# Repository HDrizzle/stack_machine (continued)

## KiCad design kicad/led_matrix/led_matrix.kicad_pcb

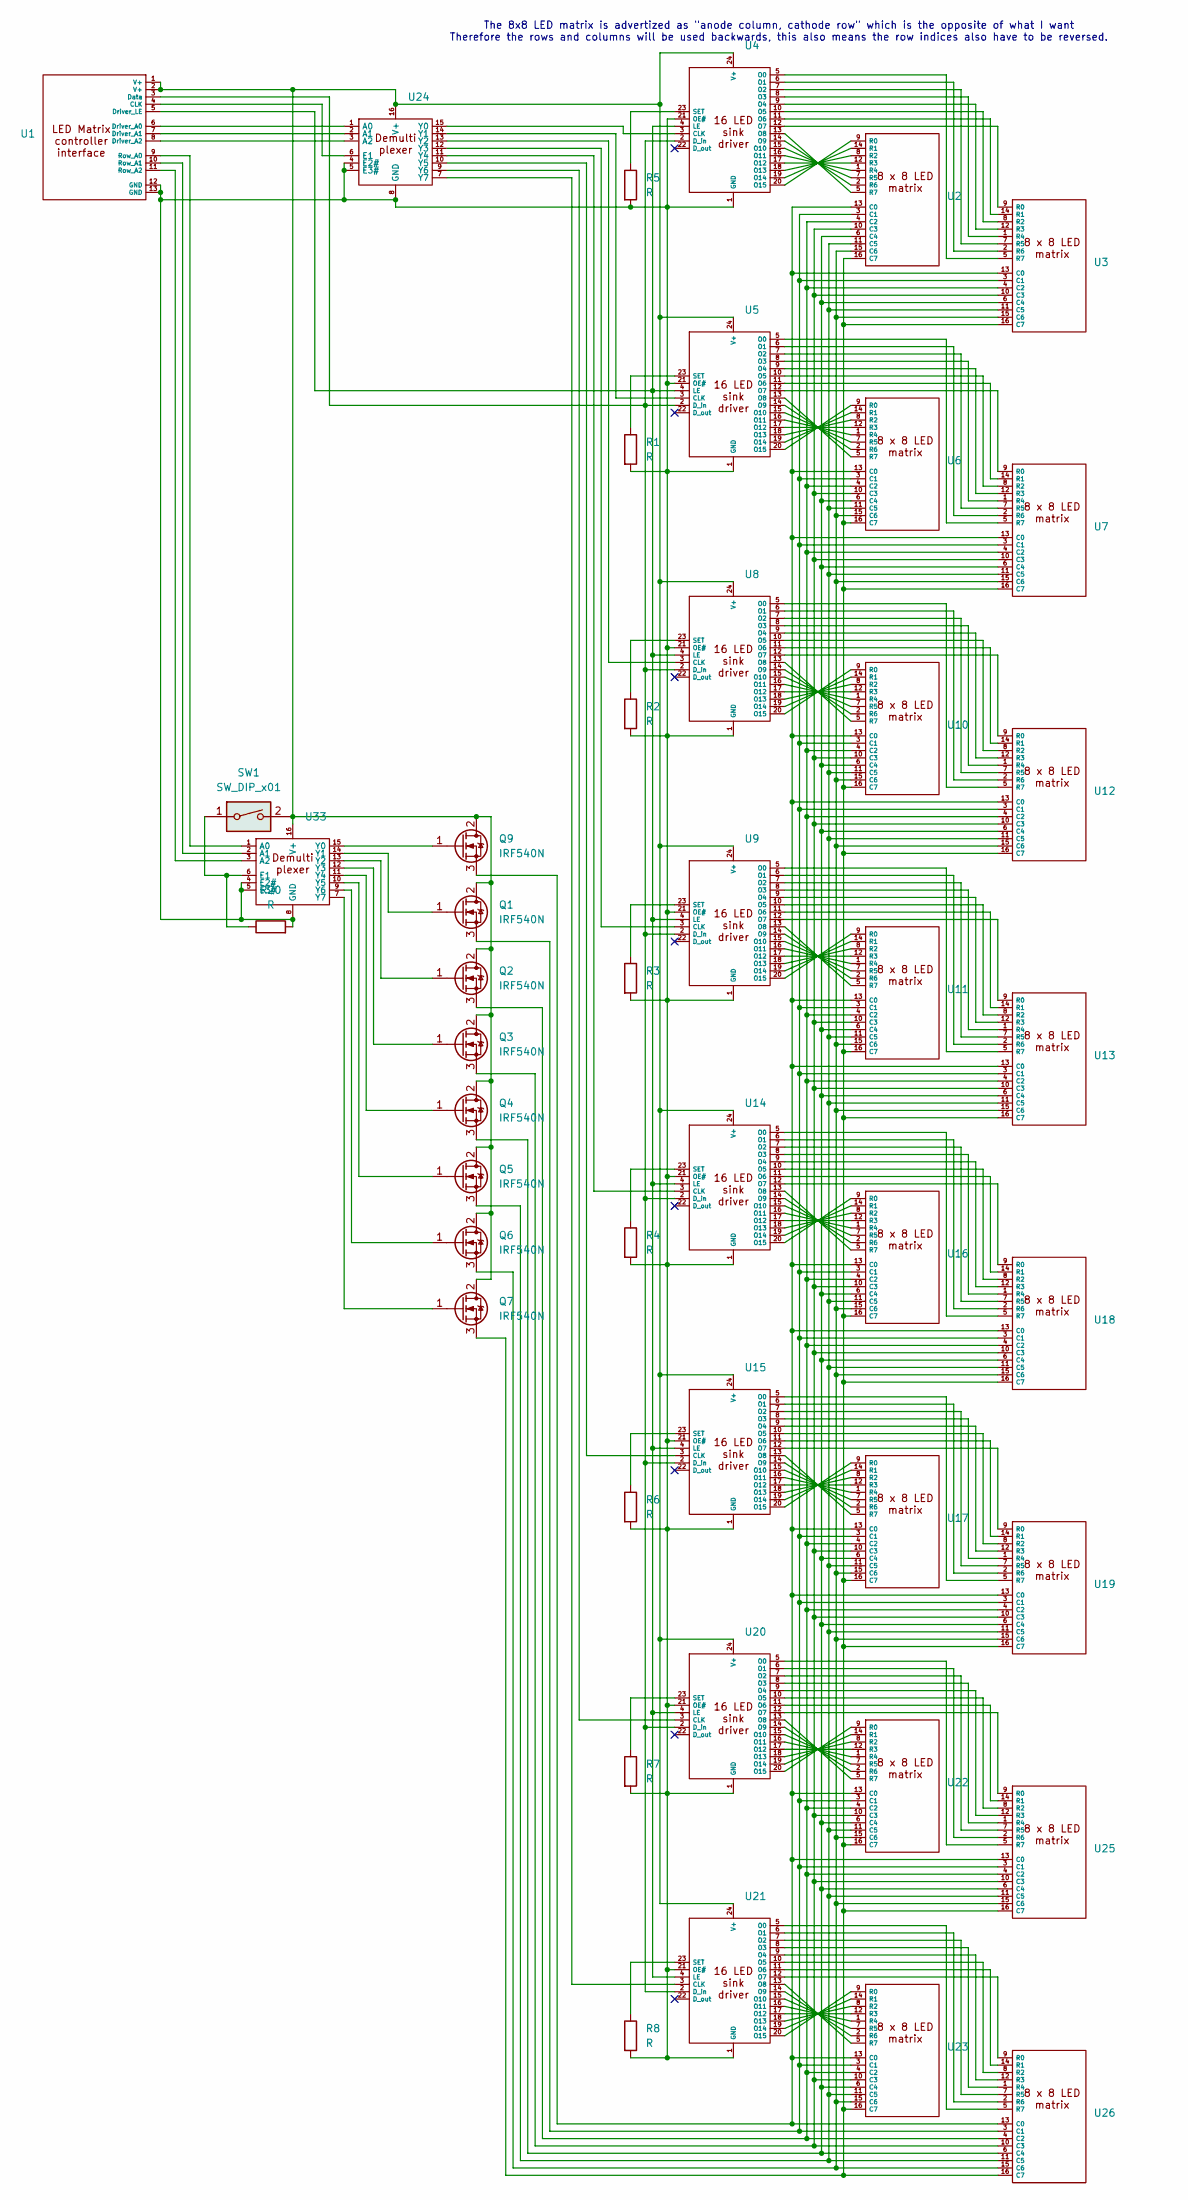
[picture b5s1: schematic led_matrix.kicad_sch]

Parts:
Q1, Q2, Q3, Q4, Q5, Q6, Q7, Q9: IRF540N; TO-220-3_Vertical
R1, R2, R3, R4, R5, R6, R7, R8, R20: R; 0.4_pitch_resistor
SW1: SW_DIP_x01; SW_DIP_SPSTx01_Slide_6.7x4.1mm_W7.62mm_P2.54mm_LowProfile
U1: PinHeader_1x13_P2.54mm_Vertical
U2, U3, U6, U7, U10, U11, U12, U13, U16, U17, U18, U19, U22, U23, U25, U26: 8_x_8_led_matrix_KWM-30881CVB
U4, U5, U8, U9, U14, U15, U20, U21: DIP-24_W7.62mm
U24, U33: DIP-16_W7.62mm

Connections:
unnamed: Q1.2 (D), Q2.2 (D), Q3.2 (D), Q4.2 (D), Q5.2 (D), Q6.2 (D), Q7.2 (D), Q9.2 (D), SW1.2, U1.1 (V+), U1.2 (V+), U4.24 (V+), U5.24 (V+), U8.24 (V+), U9.24 (V+), U14.24 (V+), U15.24 (V+), U20.24 (V+), U21.24 (V+), U24.16 (V+), U33.16 (V+)
unnamed: Q1.1 (G), U33.14 (Y1)
unnamed: Q1.3 (S), U2.3 (C1), U3.3 (C1), U6.3 (C1), U7.3 (C1), U10.3 (C1), U11.3 (C1), U12.3 (C1), U13.3 (C1), U16.3 (C1), U17.3 (C1), U18.3 (C1), U19.3 (C1), U22.3 (C1), U23.3 (C1), U25.3 (C1), U26.3 (C1)
unnamed: Q2.1 (G), U33.13 (Y2)
unnamed: Q2.3 (S), U2.4 (C2), U3.4 (C2), U6.4 (C2), U7.4 (C2), U10.4 (C2), U11.4 (C2), U12.4 (C2), U13.4 (C2), U16.4 (C2), U17.4 (C2), U18.4 (C2), U19.4 (C2), U22.4 (C2), U23.4 (C2), U25.4 (C2), U26.4 (C2)
unnamed: Q3.1 (G), U33.12 (Y3)
unnamed: Q3.3 (S), U2.10 (C3), U3.10 (C3), U6.10 (C3), U7.10 (C3), U10.10 (C3), U11.10 (C3), U12.10 (C3), U13.10 (C3), U16.10 (C3), U17.10 (C3), U18.10 (C3), U19.10 (C3), U22.10 (C3), U23.10 (C3), U25.10 (C3), U26.10 (C3)
unnamed: Q4.1 (G), U33.11 (Y4)
unnamed: Q4.3 (S), U2.6 (C4), U3.6 (C4), U6.6 (C4), U7.6 (C4), U10.6 (C4), U11.6 (C4), U12.6 (C4), U13.6 (C4), U16.6 (C4), U17.6 (C4), U18.6 (C4), U19.6 (C4), U22.6 (C4), U23.6 (C4), U25.6 (C4), U26.6 (C4)
unnamed: Q5.1 (G), U33.10 (Y5)
unnamed: Q5.3 (S), U2.11 (C5), U3.11 (C5), U6.11 (C5), U7.11 (C5), U10.11 (C5), U11.11 (C5), U12.11 (C5), U13.11 (C5), U16.11 (C5), U17.11 (C5), U18.11 (C5), U19.11 (C5), U22.11 (C5), U23.11 (C5), U25.11 (C5), U26.11 (C5)
unnamed: Q6.1 (G), U33.9 (Y6)
unnamed: Q6.3 (S), U2.15 (C6), U3.15 (C6), U6.15 (C6), U7.15 (C6), U10.15 (C6), U11.15 (C6), U12.15 (C6), U13.15 (C6), U16.15 (C6), U17.15 (C6), U18.15 (C6), U19.15 (C6), U22.15 (C6), U23.15 (C6), U25.15 (C6), U26.15 (C6)
unnamed: Q7.1 (G), U33.7 (Y7)
unnamed: Q7.3 (S), U2.16 (C7), U3.16 (C7), U6.16 (C7), U7.16 (C7), U10.16 (C7), U11.16 (C7), U12.16 (C7), U13.16 (C7), U16.16 (C7), U17.16 (C7), U18.16 (C7), U19.16 (C7), U22.16 (C7), U23.16 (C7), U25.16 (C7), U26.16 (C7)
unnamed: Q9.1 (G), U33.15 (Y0)
unnamed: Q9.3 (S), U2.13 (C0), U3.13 (C0), U6.13 (C0), U7.13 (C0), U10.13 (C0), U11.13 (C0), U12.13 (C0), U13.13 (C0), U16.13 (C0), U17.13 (C0), U18.13 (C0), U19.13 (C0), U22.13 (C0), U23.13 (C0), U25.13 (C0), U26.13 (C0)
unnamed: U1.4 (CLK), U24.6 (E1)
unnamed: U1.3 (Data), U4.2 (D_in), U5.2 (D_in), U8.2 (D_in), U9.2 (D_in), U14.2 (D_in), U15.2 (D_in), U20.2 (D_in), U21.2 (D_in)
unnamed: U1.6 (Driver_A0), U24.1 (A0)
unnamed: U1.7 (Driver_A1), U24.2 (A1)
unnamed: U1.8 (Driver_A2), U24.3 (A2)
unnamed: U1.5 (Driver_LE), U4.4 (LE), U5.4 (LE), U8.4 (LE), U9.4 (LE), U14.4 (LE), U15.4 (LE), U20.4 (LE), U21.4 (LE)
unnamed: U1.9 (Row_A0), U33.1 (A0)
unnamed: U1.10 (Row_A1), U33.2 (A1)
unnamed: U1.11 (Row_A2), U33.3 (A2)
unnamed: U2.9 (R0), U4.20 (O15)
unnamed: U2.14 (R1), U4.19 (O14)
unnamed: U2.8 (R2), U4.18 (O13)
unnamed: U2.12 (R3), U4.17 (O12)
unnamed: U2.1 (R4), U4.16 (O11)
unnamed: U2.7 (R5), U4.15 (O10)
unnamed: U2.2 (R6), U4.14 (O9)
unnamed: U2.5 (R7), U4.13 (O8)
unnamed: U3.9 (R0), U4.12 (O7)
unnamed: U3.14 (R1), U4.11 (O6)
unnamed: U3.8 (R2), U4.10 (O5)
unnamed: U3.12 (R3), U4.9 (O4)
unnamed: U3.1 (R4), U4.8 (O3)
unnamed: U3.7 (R5), U4.7 (O2)
unnamed: U3.2 (R6), U4.6 (O1)
unnamed: U3.5 (R7), U4.5 (O0)
unnamed: R5.1, U4.23 (SET)
unnamed: U5.5 (O0), U7.5 (R7)
unnamed: U5.6 (O1), U7.2 (R6)
unnamed: U5.7 (O2), U7.7 (R5)
unnamed: U5.8 (O3), U7.1 (R4)
unnamed: U5.9 (O4), U7.12 (R3)
unnamed: U5.10 (O5), U7.8 (R2)
unnamed: U5.11 (O6), U7.14 (R1)
unnamed: U5.12 (O7), U7.9 (R0)
unnamed: U5.13 (O8), U6.5 (R7)
unnamed: U5.14 (O9), U6.2 (R6)
unnamed: U5.15 (O10), U6.7 (R5)
unnamed: U5.16 (O11), U6.1 (R4)
unnamed: U5.17 (O12), U6.12 (R3)
unnamed: U5.18 (O13), U6.8 (R2)
unnamed: U5.19 (O14), U6.14 (R1)
unnamed: U5.20 (O15), U6.9 (R0)
unnamed: R1.1, U5.23 (SET)
unnamed: R2.1, U8.23 (SET)
unnamed: R3.1, U9.23 (SET)
unnamed: U8.20 (O15), U10.9 (R0)
unnamed: U8.19 (O14), U10.14 (R1)
unnamed: U8.18 (O13), U10.8 (R2)
unnamed: U8.17 (O12), U10.12 (R3)
unnamed: U8.16 (O11), U10.1 (R4)
unnamed: U8.15 (O10), U10.7 (R5)
unnamed: U8.14 (O9), U10.2 (R6)
unnamed: U8.13 (O8), U10.5 (R7)
unnamed: U9.20 (O15), U11.9 (R0)
unnamed: U9.19 (O14), U11.14 (R1)
unnamed: U9.18 (O13), U11.8 (R2)
unnamed: U9.17 (O12), U11.12 (R3)
unnamed: U9.16 (O11), U11.1 (R4)
unnamed: U9.15 (O10), U11.7 (R5)
unnamed: U9.14 (O9), U11.2 (R6)
unnamed: U9.13 (O8), U11.5 (R7)
unnamed: U8.12 (O7), U12.9 (R0)
unnamed: U8.11 (O6), U12.14 (R1)
unnamed: U8.10 (O5), U12.8 (R2)
unnamed: U8.9 (O4), U12.12 (R3)
unnamed: U8.8 (O3), U12.1 (R4)
unnamed: U8.7 (O2), U12.7 (R5)
unnamed: U8.6 (O1), U12.2 (R6)
unnamed: U8.5 (O0), U12.5 (R7)
unnamed: U9.12 (O7), U13.9 (R0)
unnamed: U9.11 (O6), U13.14 (R1)
unnamed: U9.10 (O5), U13.8 (R2)
unnamed: U9.9 (O4), U13.12 (R3)
unnamed: U9.8 (O3), U13.1 (R4)
unnamed: U9.7 (O2), U13.7 (R5)
unnamed: U9.6 (O1), U13.2 (R6)
unnamed: U9.5 (O0), U13.5 (R7)
unnamed: U14.3 (CLK), U24.11 (Y4)
unnamed: R1.2, R2.2, R3.2, R4.2, R5.2, R6.2, R7.2, R8.2, R20.2, U1.12 (GND), U1.13 (GND), U4.1 (GND), U4.21 (OE#), U5.1 (GND), U5.21 (OE#), U8.1 (GND), U8.21 (OE#), U9.1 (GND), U9.21 (OE#), U14.1 (GND), U14.21 (OE#), U15.1 (GND), U15.21 (OE#), U20.1 (GND), U20.21 (OE#), U21.1 (GND), U21.21 (OE#), U24.4 (E2#), U24.5 (E3#), U24.8 (GND), U33.4 (E2#), U33.5 (E3#), U33.8 (GND)
unnamed: U14.5 (O0), U18.5 (R7)
unnamed: U14.6 (O1), U18.2 (R6)
unnamed: U14.7 (O2), U18.7 (R5)
unnamed: U14.8 (O3), U18.1 (R4)
unnamed: U14.9 (O4), U18.12 (R3)
unnamed: U14.10 (O5), U18.8 (R2)
unnamed: U14.11 (O6), U18.14 (R1)
unnamed: U14.12 (O7), U18.9 (R0)
unnamed: U14.13 (O8), U16.5 (R7)
unnamed: U14.14 (O9), U16.2 (R6)
unnamed: U14.15 (O10), U16.7 (R5)
unnamed: U14.16 (O11), U16.1 (R4)
unnamed: U14.17 (O12), U16.12 (R3)
unnamed: U14.18 (O13), U16.8 (R2)
unnamed: U14.19 (O14), U16.14 (R1)
unnamed: U14.20 (O15), U16.9 (R0)
unnamed: R4.1, U14.23 (SET)
unnamed: U15.3 (CLK), U24.10 (Y5)
unnamed: U15.5 (O0), U19.5 (R7)
unnamed: U15.6 (O1), U19.2 (R6)
unnamed: U15.7 (O2), U19.7 (R5)
unnamed: U15.8 (O3), U19.1 (R4)
unnamed: U15.9 (O4), U19.12 (R3)
unnamed: U15.10 (O5), U19.8 (R2)
unnamed: U15.11 (O6), U19.14 (R1)
unnamed: U15.12 (O7), U19.9 (R0)
unnamed: U15.13 (O8), U17.5 (R7)
unnamed: U15.14 (O9), U17.2 (R6)
unnamed: U15.15 (O10), U17.7 (R5)
unnamed: U15.16 (O11), U17.1 (R4)
unnamed: U15.17 (O12), U17.12 (R3)
unnamed: U15.18 (O13), U17.8 (R2)
unnamed: U15.19 (O14), U17.14 (R1)
unnamed: U15.20 (O15), U17.9 (R0)
unnamed: R6.1, U15.23 (SET)
unnamed: U20.3 (CLK), U24.9 (Y6)
unnamed: U20.5 (O0), U25.5 (R7)
unnamed: U20.6 (O1), U25.2 (R6)
unnamed: U20.7 (O2), U25.7 (R5)
unnamed: U20.8 (O3), U25.1 (R4)
unnamed: U20.9 (O4), U25.12 (R3)
unnamed: U20.10 (O5), U25.8 (R2)
unnamed: U20.11 (O6), U25.14 (R1)
unnamed: U20.12 (O7), U25.9 (R0)
unnamed: U20.13 (O8), U22.5 (R7)
unnamed: U20.14 (O9), U22.2 (R6)
unnamed: U20.15 (O10), U22.7 (R5)
unnamed: U20.16 (O11), U22.1 (R4)
unnamed: U20.17 (O12), U22.12 (R3)
unnamed: U20.18 (O13), U22.8 (R2)
unnamed: U20.19 (O14), U22.14 (R1)
unnamed: U20.20 (O15), U22.9 (R0)
unnamed: R7.1, U20.23 (SET)
unnamed: U21.3 (CLK), U24.7 (Y7)
unnamed: U21.5 (O0), U26.5 (R7)
unnamed: U21.6 (O1), U26.2 (R6)
unnamed: U21.7 (O2), U26.7 (R5)
unnamed: U21.8 (O3), U26.1 (R4)
unnamed: U21.9 (O4), U26.12 (R3)
unnamed: U21.10 (O5), U26.8 (R2)
unnamed: U21.11 (O6), U26.14 (R1)
unnamed: U21.12 (O7), U26.9 (R0)
unnamed: U21.13 (O8), U23.5 (R7)
unnamed: U21.14 (O9), U23.2 (R6)
unnamed: U21.15 (O10), U23.7 (R5)
unnamed: U21.16 (O11), U23.1 (R4)
unnamed: U21.17 (O12), U23.12 (R3)
unnamed: U21.18 (O13), U23.8 (R2)
unnamed: U21.19 (O14), U23.14 (R1)
unnamed: U21.20 (O15), U23.9 (R0)
unnamed: R8.1, U21.23 (SET)
unnamed: U4.3 (CLK), U24.15 (Y0)
unnamed: U5.3 (CLK), U24.14 (Y1)
unnamed: U8.3 (CLK), U24.13 (Y2)
unnamed: U9.3 (CLK), U24.12 (Y3)
unnamed: R20.1, SW1.1, U33.6 (E1)

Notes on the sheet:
The 8x8 LED matrix is advertized as "anode column, cathode row" which is the opposite of what I want Therefore the rows and columns will be used backwards, this also means the row indices also have to be reversed.

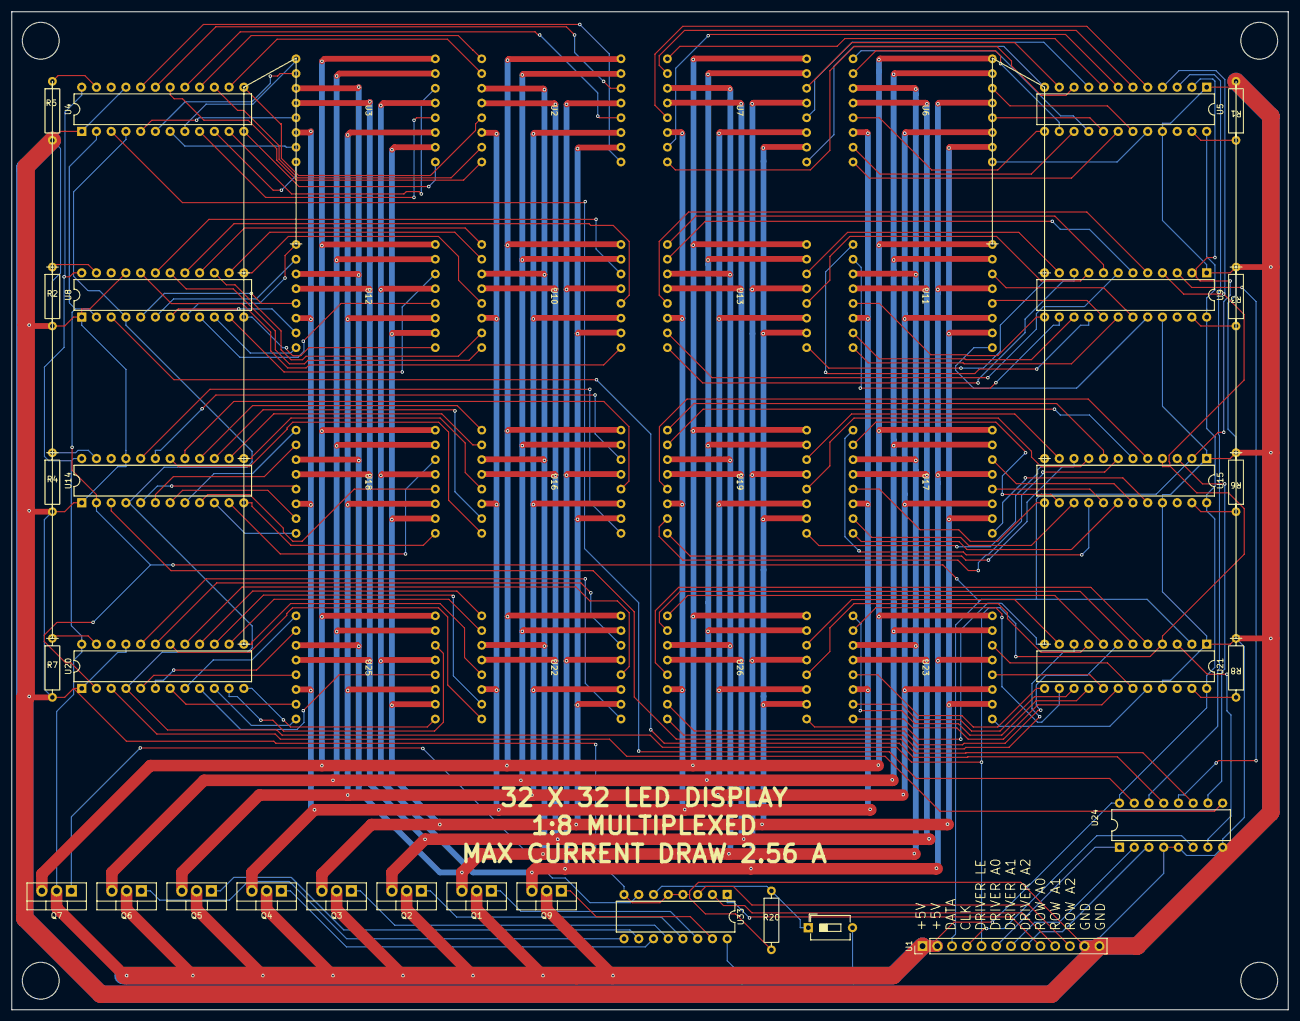
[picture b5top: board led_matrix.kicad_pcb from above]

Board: 2 copper layers, 220.0 x 172.0 mm, 45 parts (0 on the bottom side), 172 nets.

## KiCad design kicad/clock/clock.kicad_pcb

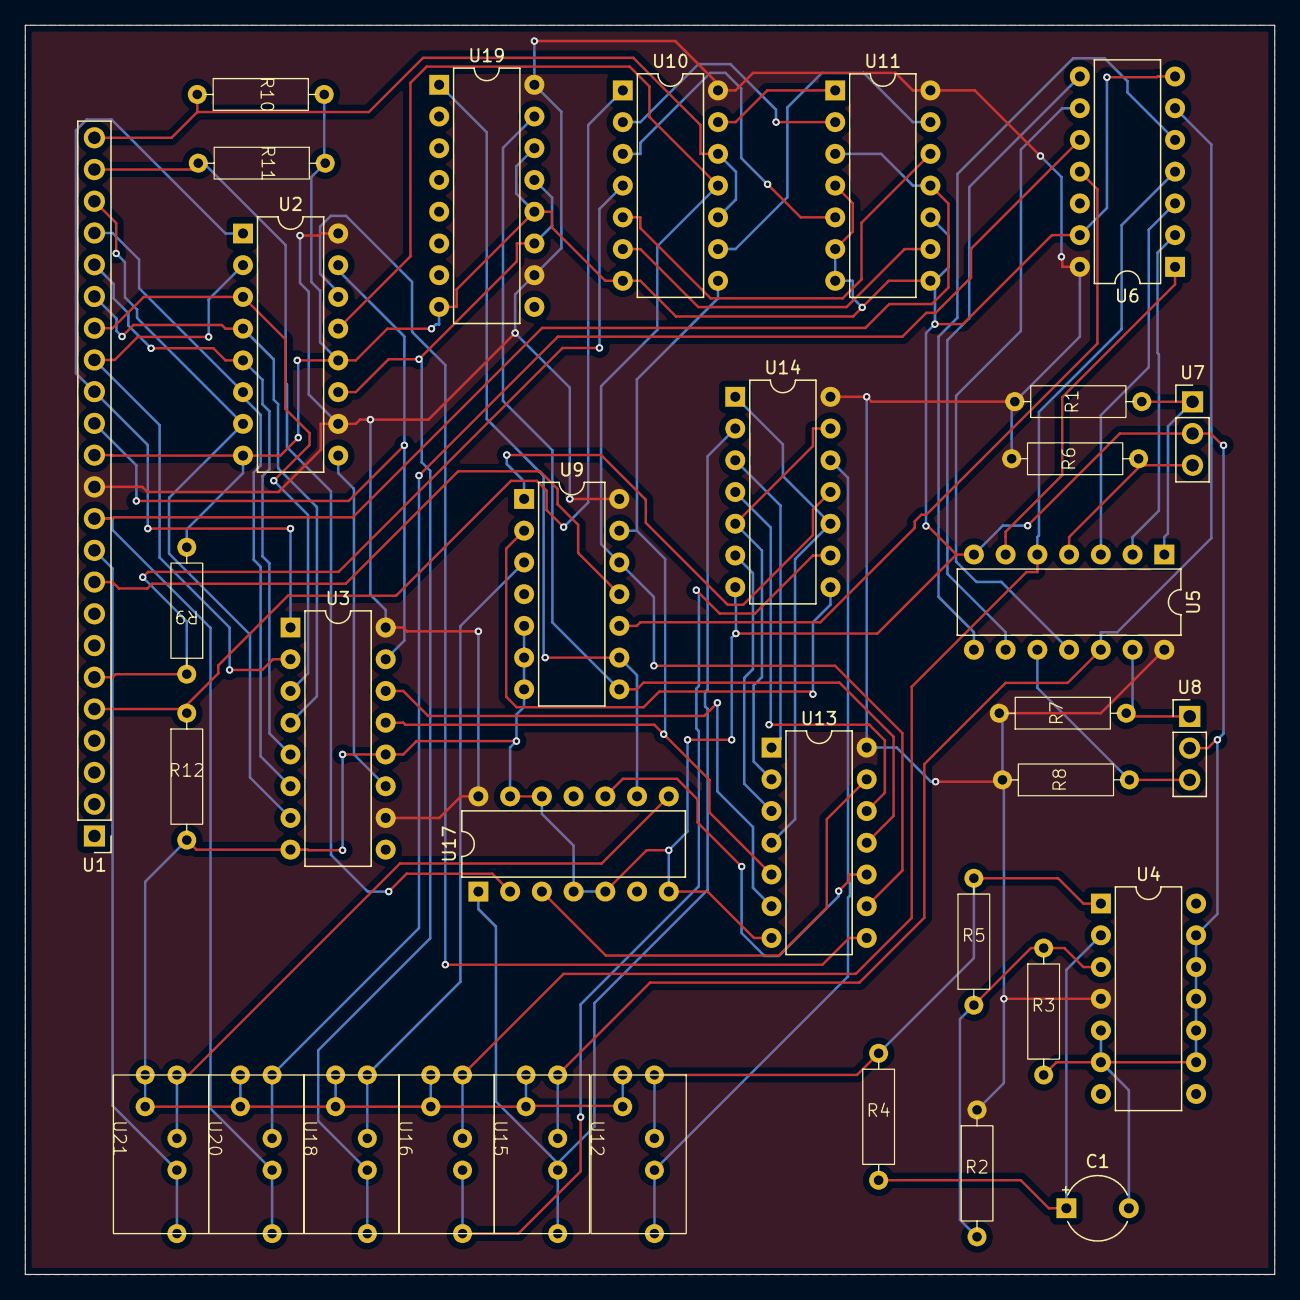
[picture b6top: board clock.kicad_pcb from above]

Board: 2 copper layers, 100.0 x 100.0 mm, 34 parts (0 on the bottom side), 62 nets.

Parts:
C1: C; CP_Radial_Tantal_D5.0mm_P5.00mm
R1, R2, R3, R4, R5, R6, R7, R8: R; 0.4_pitch_resistor
R9, R10, R11, R12: 1k; 0.4_pitch_resistor
U1: PinHeader_1x23_P2.54mm_Vertical
U2, U3, U19: DIP-16_W7.62mm
U4, U5, U6, U9, U10, U11, U13, U14, U17: DIP-14_W7.62mm
U7, U8: PinHeader_1x03_P2.54mm_Vertical
U12, U15, U16, U18, U20, U21: jumper

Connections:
unnamed: U1.10 (CLK_A), U21.3 (OUT)
unnamed: U1.11 (CLK_B), U11.3 (0CLK), U11.11 (1CLK), U20.3 (OUT)
unnamed: U1.14 (D0), U2.15 (Q0), U3.15 (Q0)
unnamed: U1.15 (D1), U2.1 (Q1), U3.1 (Q1)
unnamed: U1.16 (D2), U2.2 (Q2), U3.2 (Q2)
unnamed: U1.17 (D3), U2.3 (Q3), U3.3 (Q3)
unnamed: U1.18 (D4), U2.4 (Q4), U3.4 (Q4)
unnamed: U1.19 (D5), U2.5 (Q5), U3.5 (Q5)
unnamed: U1.20 (D6), U2.6 (Q6), U3.6 (Q6)
unnamed: U1.21 (D7), U2.7 (Q7), U3.7 (Q7)
unnamed: R10.2, U1.23 (ENABLE), U10.10 (4A), U10.12 (3B)
unnamed: R11.2, U1.22 (FAULT), U17.2 (1B)
unnamed: C1.2, R3.2, R9.2, R10.1, R11.1, R12.2, U1.13 (GND), U2.8 (GND), U2.12 (CCKEN#), U3.8 (GND), U3.12 (CCKEN#), U4.5 (IN+_2), U4.6 (IN-_2), U4.9 (IN-_3), U4.10 (IN+_3), U4.11 (GND), U4.12 (IN+_4), U4.13 (IN-_4), U5.7 (GND), U6.7 (GND), U6.13 (I5), U7.2 (2_(middle)), U8.2 (2_(middle)), U9.5 (1A), U9.6 (1B), U9.7 (GND), U10.7 (GND), U11.4 (0RESET), U11.6 (0SET), U11.7 (GND), U11.8 (1SET), U11.10 (1RESET), U12.2 (GND), U13.7 (GND), U14.7 (GND), U15.2 (GND), U16.2 (GND), U17.4 (2A), U17.5 (2B), U17.7 (GND), U17.12 (3B), U17.13 (3A), U18.2 (GND), U19.8 (GND), U19.12 (CCKEN#), U19.14 (OE#), U20.2 (GND), U21.2 (GND)
unnamed: U1.9 (READ_READY), U9.11 (Q3)
unnamed: R1.1, R2.1, R6.1, R7.1, R8.1, U1.12 (V+), U2.10 (CCLR#), U2.16 (V+), U3.10 (CCLR#), U3.16 (V+), U4.4 (V+), U5.14 (V+), U6.14 (V+), U9.14 (V+), U10.14 (V+), U11.14 (V+), U13.14 (V+), U14.14 (V+), U17.14 (V+), U19.10 (CCLR#), U19.16 (V+)
unnamed: R12.1, U1.5 (WRITE_0), U10.1 (1A)
unnamed: R9.1, U1.6 (WRITE_1), U10.4 (2A)
unnamed: U2.9 (RCO#), U3.11 (CCLK)
unnamed: R2.2, R3.1, R5.2, U4.3 (IN+_1)
unnamed: C1.1, R4.2, U4.2 (IN-_1)
unnamed: R1.2, U5.1 (1A), U7.1
unnamed: U5.2 (1B), U6.2 (O0)
unnamed: U5.3 (1Q), U6.3 (I1)
unnamed: R6.2, U5.4 (2A), U7.3
unnamed: U5.6 (2Q), U6.1 (I0)
unnamed: R7.2, U5.13 (3A), U8.1
unnamed: U5.11 (3Q), U6.9 (I3)
unnamed: R8.2, U5.10 (4A), U8.3
unnamed: U5.9 (4B), U6.8 (03)
unnamed: U5.8 (4Q), U6.5 (I2)
unnamed: U6.11 (I4), U9.10 (Q2)
unnamed: U10.2 (1B), U11.2 (0Q#)
unnamed: U10.3 (1Q), U11.5 (0D)
unnamed: U10.5 (2B), U11.12 (1Q3)
unnamed: U10.6 (2Q), U11.9 (1D)
unnamed: U10.13 (3A), U11.1 (0Q)
unnamed: U2.13 (RCLK), U9.12 (3A), U10.11 (3Q), U13.9 (I3)
unnamed: U10.9 (4B), U11.13 (1Q)
unnamed: U3.13 (RCLK), U9.13 (3B), U10.8 (4Q), U13.5 (I2)
unnamed: R4.1, R5.1, U4.1 (OUT_1), U12.1 (IN)
unnamed: U12.3 (OUT), U14.12 (3B)
unnamed: U2.14 (OE#), U13.8 (03)
unnamed: U13.1 (I0), U14.3 (1Q)
unnamed: U13.3 (I1), U14.6 (2Q)
unnamed: U9.8 (2A), U13.11 (I4), U19.15 (Q0)
unnamed: U13.13 (I5), U17.3 (1Q)
unnamed: U13.2 (O0), U14.5 (2B), U14.13 (3A)
unnamed: U13.4 (O1), U14.1 (1A), U14.10 (4A)
unnamed: U3.14 (OE#), U13.6 (O2)
unnamed: U13.10 (O4), U17.10 (4A)
unnamed: U13.12 (O5), U14.4 (2A)
unnamed: U14.2 (1B), U15.3 (OUT), U17.1 (1A)
unnamed: U9.1 (0A), U14.11 (3Q)
unnamed: U14.9 (4B), U16.3 (OUT)
unnamed: U9.2 (0B), U14.8 (4Q)
unnamed: U5.12 (3B), U6.6 (O2), U15.1 (IN)
unnamed: U5.5 (2B), U6.4 (O1), U16.1 (IN)
unnamed: U9.9 (2B), U17.9 (4B), U19.1 (Q1)
unnamed: U17.8 (4Q), U21.1 (IN)
unnamed: U9.3 (Q0), U18.1 (IN)
unnamed: U2.11 (CCLK), U18.3 (OUT), U19.11 (CCLK), U19.13 (RCLK)
unnamed: U6.10 (O4), U20.1 (IN)
